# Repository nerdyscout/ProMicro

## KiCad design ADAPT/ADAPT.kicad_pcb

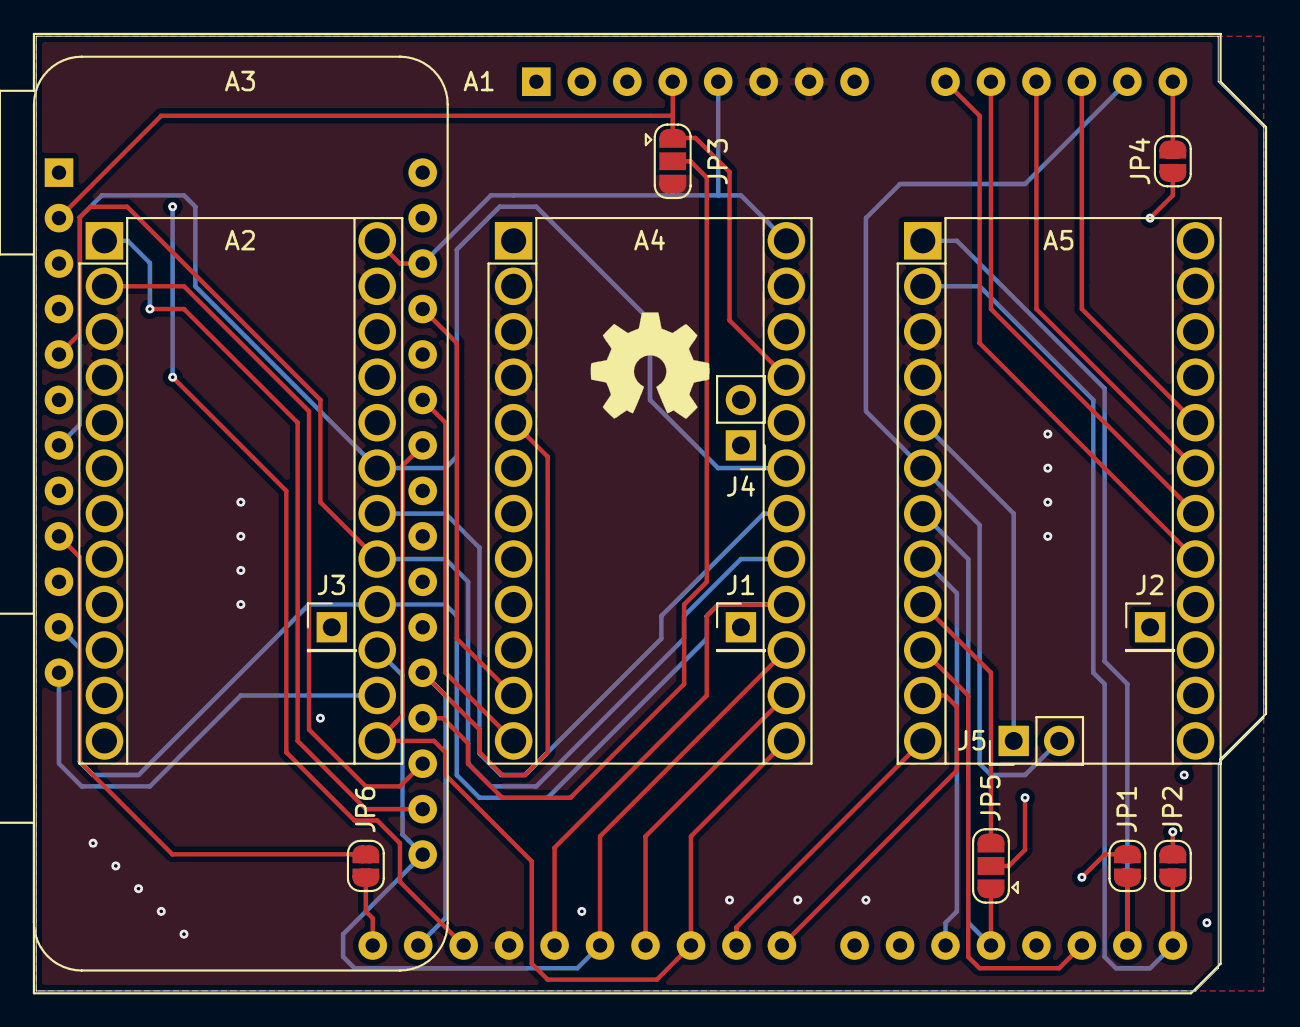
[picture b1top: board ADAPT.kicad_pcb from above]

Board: 4 copper layers, 68.6 x 53.3 mm, 17 parts (0 on the bottom side), 29 nets.

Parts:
A1: Arduino_UNO_R3
A2, A4, A5: Sparkfun_Pro_Micro; ProMicro
A3: Adafruit_Feather_Generic; Adafruit_Feather
J1, J2, J3: VBAT; PinHeader_1x01_P2.54mm_Vertical
J4, J5: Conn_01x02; PinHeader_1x02_P2.54mm_Vertical
JP1, JP2, JP4, JP6: SolderJumper_2_Open; SolderJumper-2_P1.3mm_Open_RoundedPad1.0x1.5mm
JP3, JP5: SolderJumper_3_Open; SolderJumper-3_P1.3mm_Open_RoundedPad1.0x1.5mm
LOGO1: Logo_Open_Hardware_Small; OSHW-Symbol_6.7x6mm_SilkScreen

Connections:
+3V3: A1.4, A2.21, A3.2, A4.21, A5.21, JP3.1
+5V: A1.5, A2.24, A3.26, A4.24, A5.24
A0: A1.9, A2.17, A3.5, A4.17, A5.17, JP5.2
A1: A1.10, A2.18, A3.6, A4.18, A5.18
A2: A1.11, A2.19, A3.7, A4.19, A5.19
A3: A1.12, A2.20, A3.8, A4.20, A5.20
AREF: A1.30, A3.3
BTN: A2.9, A4.9, A5.9, JP5.3
CIPO: A1.27, A2.15, A3.13, A4.15, A5.15
COPI: A1.26, A2.14, A3.12, A4.14, A5.14
CS0: A1.25, A2.13, A3.22, A4.13, A5.13
CS1: A1.24, A2.12, A3.23, A4.12, A5.12
D8: A1.23, A2.11, A3.25, A4.11, A5.11
GND: A1.6, A1.7, A1.29, A2.3, A2.4, A2.23, A3.4, A4.3, A4.4, A4.23, A5.3, A5.4, A5.23, JP3.3
INT: A1.17, A2.10, A3.21, A4.10, A5.10
unnamed: A3.9, JP6.1
unnamed: A3.10, JP4.1
unnamed: A3.19, JP1.2
unnamed: A3.20, JP2.2
unnamed: J1.1, J2.1, J3.1
PWM: A1.20, A2.8, A3.24, A4.8, A5.8
RXD: A1.16, A2.1, A3.14, A4.1, A5.1, JP1.1
SCK: A1.28, A2.16, A3.11, A4.16, A5.16
SCL: A1.13, A1.32, A2.6, A3.18, A4.6, A5.6, J4.2, J5.2, JP6.2
SDA: A1.14, A1.31, A2.5, A3.17, A4.5, A5.5, J4.1, J5.1, JP4.2
SPARE: A3.16, JP3.2
STAT: A1.19, A2.7, A4.7, A5.7, JP5.1
TXD: A1.15, A2.2, A3.15, A4.2, A5.2, JP2.1
~RST: A1.3, A2.22, A3.1, A4.22, A5.22

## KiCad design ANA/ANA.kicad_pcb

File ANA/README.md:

# ProMicro_ANA 
This module can be mounted, back on back, to any [Arduino Pro Mini](https://www.sparkfun.com/products/11113), [Arduino Nano](https://store.arduino.cc/arduino-nano) or [Sparkfun Pro Micro](https://www.sparkfun.com/products/12587) running with 3.3V. 

## Documentation 
All files can be found on [Github](https://github.com/nerdyscout/ProMicro/tree/master/ANA).

### Schematic

### BoM
  * [interactiveHTMLBoM](https://nerdyscout.github.io/ProMicro/ANA/docs/bom/ANA-ibom.html)
  * [octopart](docs/bom/ANA-bom_octopart.csv)

## Hardware 
### Layout

### Gerbers
can be found within the Github [repository](gerbers).

## Code  (unless otherwise stated)
  * [tbd](examples/tbd/tbd.ino)

## external
### Links
  * [hackaday.io](https://hackaday.io/project/171898-promicro)

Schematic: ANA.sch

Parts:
A1: Sparkfun_Pro_Micro
C1, C3: 10µ; C_0603_1608Metric
C2, C4: 4.7µ; C_0603_1608Metric
C5, C6: 100n; C_0603_1608Metric
D1, D2: LED; LED_0603_1608Metric
J1: Conn_01x04; TerminalBlock_Phoenix_MPT-0,5-4-2.54_1x04_P2.54mm_Horizontal
JP1, JP2, JP3, JP4: SolderJumper_2_Open; SolderJumper-2_P1.3mm_Open_RoundedPad1.0x1.5mm
L1, L2: 2.2µ; L_Bourns-SRN4018
LOGO1: Logo_Open_Hardware_Small; OSHW-Symbol_6.7x6mm_SilkScreen
R1, R3: 200k; R_0603_1608Metric
R2, R4: 47k; R_0603_1608Metric
R5, R6, R9, R10: 220; R_0603_1608Metric
R7: 4k7; R_0603_1608Metric; MPN RC0402FR-074K7L
R8: 4k7; R_0603_1608Metric; MPN RC0402FR-074K7L; lcsc# C105871
U1, U3: TLV62569DDC; SOT-23-6
U2, U4: MCP4725xxx-xCH; SOT-23-6
U5, U7: INA260; TSSOP-16_4.4x5mm_P0.65mm
U6: LTV-827S; SMDIP-8_W9.53mm

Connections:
A0: A1.17 (TDI/A0), C1.1, J1.3, JP3.1, L1.1, R1.2, R6.2, U5.1 (IN+), U5.2 (IN+), U5.3 (IN+), U5.12 (VBUS)
A1: A1.18 (TDO/A1), C3.1, J1.4, JP4.1, L2.1, R3.2, R10.2, U7.1 (IN+), U7.2 (IN+), U7.3 (IN+), U7.12 (VBUS)
GND: A1.3 (GND), A1.4 (GND), A1.23 (GND), C1.2, C2.2, C3.2, C4.2, C5.2, C6.2, D1.1 (K), D2.1 (K), JP1.2, R2.1, R4.1, U1.2 (GND), U2.2 (VSS), U2.6 (A0), U3.2 (GND), U4.2 (VSS), U5.4 (A1), U5.5 (A0), U5.6 (GND), U5.11 (GND), U6.2, U6.4, U7.5 (A0), U7.6 (GND), U7.11 (GND)
unnamed: C2.1, C4.1, J1.2, JP2.1, U1.1 (EN), U1.4 (VIN), U3.1 (EN), U3.4 (VIN)
unnamed: D1.2 (A), R5.1
unnamed: D2.2 (A), R9.1
unnamed: J1.1, JP1.1, U6.5, U6.7
unnamed: JP3.2, U5.14 (IN-), U5.15 (IN-), U5.16 (IN-), U6.6
unnamed: JP4.2, U6.8, U7.14 (IN-), U7.15 (IN-), U7.16 (IN-)
unnamed: L1.2, U1.3 (SW)
unnamed: L2.2, U3.3 (SW)
unnamed: R1.1, R2.2, U1.6 (FB), U2.1 (VOUT)
unnamed: R3.1, R4.2, U3.6 (FB), U4.1 (VOUT)
unnamed: R5.2, U5.7 (ALERT)
unnamed: R6.1, U6.1
unnamed: R9.2, U7.7 (ALERT)
unnamed: R10.1, U6.3
SCL: A1.6 (SCL/D3), R7.1, U2.5 (SCL), U4.5 (SCL), U5.9 (SCL), U7.9 (SCL)
SDA: A1.5 (SDA/D2), R8.1, U2.4 (SDA), U4.4 (SDA), U5.8 (SDA), U7.8 (SDA)
VCC: A1.21 (VCC), C5.1, C6.1, JP2.2, R7.2, R8.2, U2.3 (VDD), U4.3 (VDD), U4.6 (A0), U5.10 (VS), U7.4 (A1), U7.10 (VS)

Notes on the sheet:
opto isolated switch with current sensing
analog out
SCK
CIPO
COPI
CS0
CS1
STAT
PWM
BTN
INT
RXD
TXD
~RST
GND
Vin

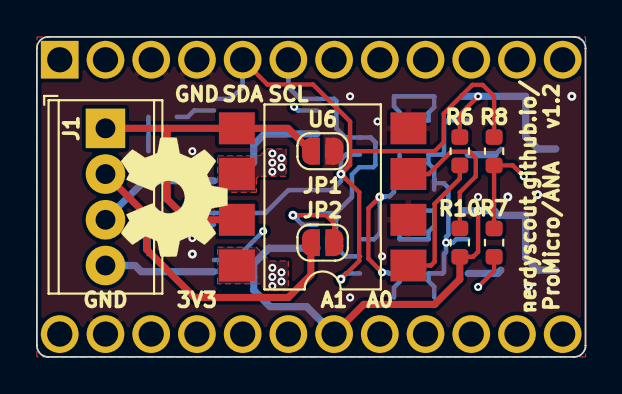
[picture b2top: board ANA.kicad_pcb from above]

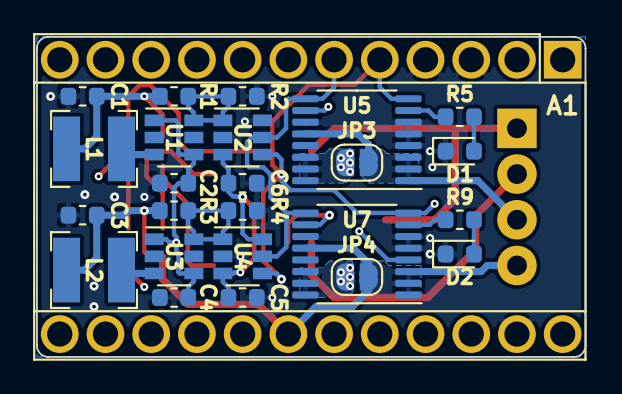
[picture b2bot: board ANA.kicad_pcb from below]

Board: 4 copper layers, 30.5 x 17.8 mm, 34 parts (25 on the bottom side), 20 nets.

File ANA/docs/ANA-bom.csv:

References;Description;Part;Value;Qty;mpn;lcsc#
A1;;Sparkfun_Pro_Micro;Sparkfun_Pro_Micro;1;;
C5 C6;Unpolarized capacitor;C;100n;2;;
C2 C4;Unpolarized capacitor;C;4.7µ;2;;
C1 C3;Unpolarized capacitor;C;10µ;2;;
D1 D2;Light emitting diode;LED;LED;2;;
J1;Generic connector, single row, 01x04, script generated (kicad-library-utils/schlib/autogen/connector/);Conn_01x04;Conn_01x04;1;;
L1 L2;Inductor;L;2.2µ;2;;
R5 R6 R9 R10;Resistor;R;220;4;;
R7 R8;Resistor;R;4k7;2;RC0402FR-074K7L;C105871
R2 R4;Resistor;R;47k;2;;
R1 R3;Resistor;R;200k;2;;
U5 U7;Current/power/voltage monitor with Integrated 2mΩ Shunt Resistor, 2.7V - 5.5V, I2C, TSSOP-16;INA260;INA260;2;;
U6;DC Optocoupler, Vce 35V, CTR 50%, SMDIP-8;LTV-827S;LTV-827S;1;;
U2 U4;12-bit Digital-to-Analog Converter, integrated EEPROM, I2C interface, SOT-23-6;MCP4725xxx-xCH;MCP4725xxx-xCH;2;;
U1 U3;High Efficiency Synchronous Buck Converter, Adjustable Output 0.6V-5.5V, 2A, SOT-23-6;TLV62569DDC;TLV62569DDC;2;;

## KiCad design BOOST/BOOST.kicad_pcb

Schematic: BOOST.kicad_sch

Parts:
A1: Sparkfun_Pro_Micro; ProMicro
C1, C4: 10µ; C_0603_1608Metric; MPN CL10A106KP8NNNC
C2, C5: 100n; C_0603_1608Metric; MPN CL10B104KO8NNNC
C3, C7: 4.7µ; C_0603_1608Metric; MPN CL10A475KO8NNNC
C6: 1µ; C_0603_1608Metric; MPN C0603X105K9RACAUTO
D1: D; D_0603_1608Metric
F1: 500mA; Fuse_0603_1608Metric; MPN 04000025WR
J1: JST; JST_PH_S2B-PH-SM4-TB_1x02-1MP_P2.00mm_Horizontal
JP1: SolderJumper_3_Open; SolderJumper-3_P1.3mm_Open_RoundedPad1.0x1.5mm
L1: 6.8µ/2A; L_Bourns_SRN6045TA; MPN 744787068
LOGO1: Logo_Open_Hardware_Small; OSHW-Symbol_6.7x6mm_SilkScreen
R1, R2, R6: 390k; R_0603_1608Metric; MPN 0603WAF3903T5E
R3: 2k; R_0603_1608Metric; MPN 0603WAF2001T5E
R4, R8: 200k; R_0603_1608Metric; MPN 0603WAF2003T5E
R5: 2.4M; R_0603_1608Metric; MPN WR06W2404FTL
R7: 1.1M; R_0603_1608Metric; MPN RM06FTN1104
TP1: VBAT; TestPoint_THTPad_D2.0mm_Drill1.0mm
U1: MCP73831-2-OT; SOT-23-5; MPN MCP73831T-2ACI/OT
U2: TPS61090; Texas_S-PVQFN-N16_EP2.7x2.7mm_ThermalVias; MPN TPS61090RSAR

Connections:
+3V3: A1.21, C6.1, C7.1, R7.1, U2.1 (VOUT), U2.15 (VOUT), U2.16 (VOUT)
/EN: R4.1, U2.11 (EN)
/VBAT: C3.2, C4.2, C5.1, J1.1, L1.1, R1.1, R4.2, R5.1, TP1.1, U1.3 (V_{BAT}), U2.8 (VBAT)
GND: A1.3, A1.4, A1.23, C1.2, C2.1, C3.1, C4.1, C5.2, C6.2, C7.2, J1.2, R2.2, R3.1, R6.2, R8.2, U1.2 (V_{SS}), U2.5 (PGND), U2.6 (PGND), U2.7 (PGND), U2.10 (SYNC), U2.13 (GND), U2.17 (PAD)
LBO: JP1.3 (B), U2.12 (LBO)
unnamed: C1.1, C2.2, D1.1 (K), U1.4 (V_{DD})
unnamed: D1.2 (A), F1.2
unnamed: JP1.1 (A), R1.2, R2.1
unnamed: L1.2, U2.3 (SW), U2.4 (SW)
unnamed: R3.2, U1.5 (PROG)
unnamed: R5.2, R6.1, U2.9 (LBI)
unnamed: R7.2, R8.1, U2.14 (FB)
STAT: A1.7, JP1.2 (C)
VBUS: A1.24, F1.1

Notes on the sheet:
R7 1.85M 1.1M (default)
Vout 5 3,3
LBI/LBO Threshold Voltage
Output Voltage
R7 = R8 * ((Vout/Vfb) -1)
R6 390k (default) 390k 390k 200k
close 1-2 read analog voltage close 2-3 read LBO status open 1 2 3 if no battery status required
R3 Icharge 2k 500mA (default) 1k 1000mA
Do only populate if you want to read analog battery voltage
R5 = R6 * ((VBat/500mV) -1)
R5 2.4M 2.5M 2.6M 1.3M
VBat 3.6 3.7 3.8 3.75
R8 200k 200k

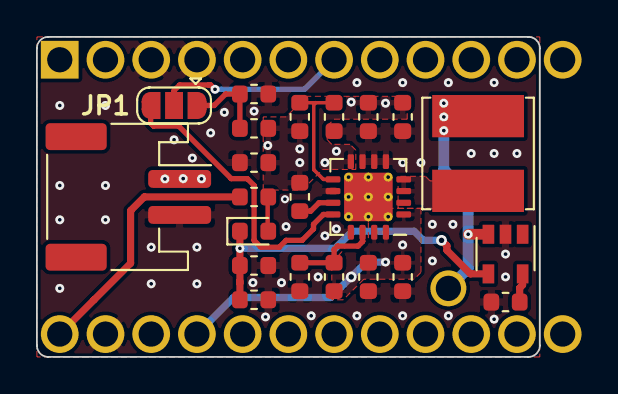
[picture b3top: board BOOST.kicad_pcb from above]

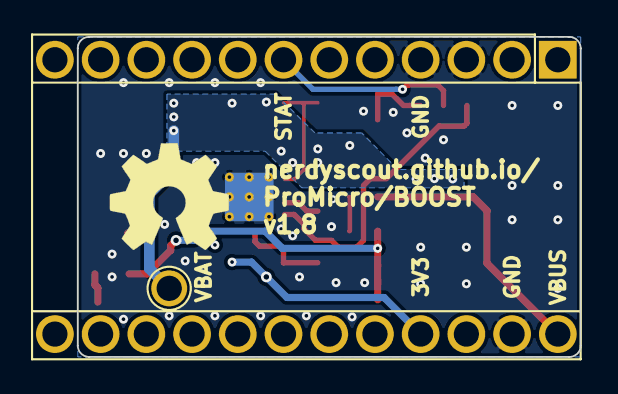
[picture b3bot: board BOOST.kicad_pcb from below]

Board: 4 copper layers, 27.9 x 17.8 mm, 25 parts (3 on the bottom side), 14 nets.

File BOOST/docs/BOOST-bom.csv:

References;Description;Part;Value;Qty;mpn;variant
C2 C5;Unpolarized capacitor;C;100n;2;CL10B104KO8NNNC;3V3, 5V
C6;Unpolarized capacitor;C;1µ;1;C0603X105K9RACAUTO;
C3 C7;Unpolarized capacitor;C;4.7µ;2;CL10A475KO8NNNC;
C1 C4;Unpolarized capacitor;C;10µ;2;CL10A106KP8NNNC;3V3, 5V
D1;Diode;D;D;1;;3V3, 5V
F1;Fuse;Fuse;500mA;1;04000025WR;
J1;Generic connector, single row, 01x02, script generated (kicad-library-utils/schlib/autogen/connector/);Conn_01x02;JST;1;;3V3, 5V
L1;Inductor;L;6.8µ/2A;1;744787068;
R3;Resistor;R;2k;1;0603WAF2001T5E;
R4 R8;Resistor;R;200k;2;0603WAF2003T5E;
R1 R2 R6;Resistor;R;390k;3;0603WAF3903T5E;
R7;Resistor;R;1.1M;1;RM06FTN1104;
R5;Resistor;R;2.4M;1;WR06W2404FTL;
U1;Single cell, Li-Ion/Li-Po charge management controller, 4.20V, Tri-State Status Output, in SOT23-5 package;MCP73831-2-OT;MCP73831-2-OT;1;MCP73831T-2ACI/OT;3V3, 5V
U2;2A Step-Up DC-DC Converter for Batteries, Isw up to 2500mA, Adjustable output voltage, QFN-16;TPS61090;TPS61090;1;TPS61090RSAR;3V3, 5V

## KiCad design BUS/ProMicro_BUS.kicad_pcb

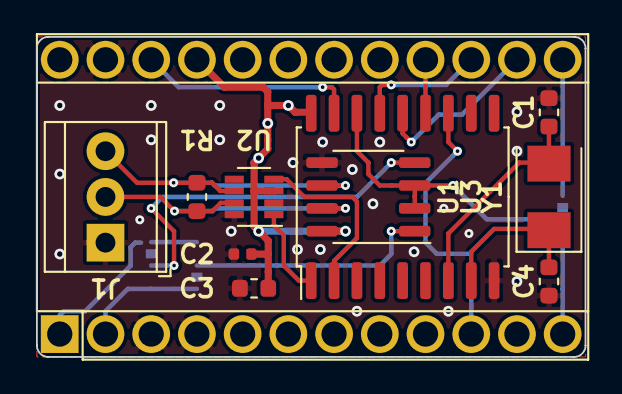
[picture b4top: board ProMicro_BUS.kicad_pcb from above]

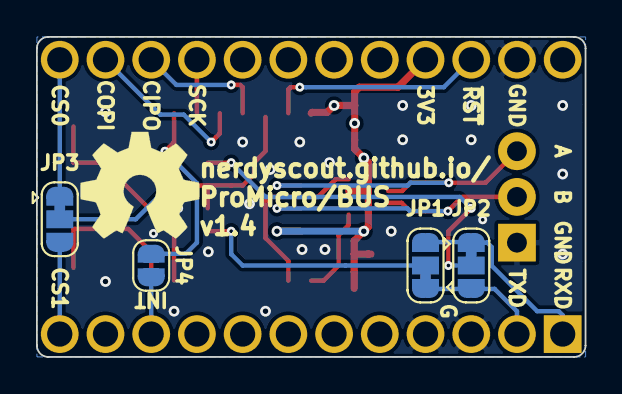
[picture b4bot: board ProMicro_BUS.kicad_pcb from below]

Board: 2 copper layers, 30.5 x 17.8 mm, 16 parts (5 on the bottom side), 21 nets.

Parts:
A1: Sparkfun_Pro_Micro
C1, C4: C; C_0603_1608Metric
C2: 100n; C_0402_1005Metric
C3: 10µ; C_0603_1608Metric
J1: Conn_01x03; TerminalBlock_TE_282834-3_1x03_P2.54mm_Horizontal
JP1, JP2, JP3: SolderJumper_3_Bridged12; SolderJumper-3_P1.3mm_Bridged12_RoundedPad1.0x1.5mm
JP4: SolderJumper_2_Open; SolderJumper-2_P1.3mm_Open_RoundedPad1.0x1.5mm
LOGO1: Logo_Open_Hardware_Small; OSHW-Symbol_6.7x6mm_SilkScreen
R1: 120; R_0603_1608Metric
U1: MAX3483; SO-8_3.9x4.9mm_P1.27mm
U2: MAX3051; SOT-23-8
U3: MCP2515-xSO; SOIC-18W_7.5x11.6mm_P1.27mm
Y1: Crystal; Crystal_SMD_5032-2Pin_5.0x3.2mm

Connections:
+3V3: A1.21, C2.1, C3.1, U1.8, U2.3, U3.18
/A: J1.3, R1.2, U1.6, U2.6
/B: J1.2, R1.1, U1.7, U2.7
CIPO: A1.15, U3.15
COPI: A1.14, U3.14
CS: JP3.2, U1.2, U1.3, U3.16
CS0: A1.13, JP3.1
CS1: A1.12, JP3.3
GND: A1.3, A1.4, A1.23, C1.1, C2.2, C3.2, C4.2, J1.1, U1.5, U2.2, U2.8, U3.9
INT: A1.10, JP4.2
unnamed: C1.2, U3.7, Y1.2
unnamed: C4.1, U3.8, Y1.1
unnamed: JP1.2, U1.1
unnamed: JP2.2, U1.4
unnamed: JP4.1, U3.12
unnamed: U2.1, U3.1
unnamed: U2.4, U3.2
RXD: A1.1, JP1.3, JP2.1
SCK: A1.16, U3.13
TXD: A1.2, JP1.1, JP2.3
~RST: A1.22, U3.17

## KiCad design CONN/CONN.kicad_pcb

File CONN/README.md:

# ProMicro_CONN 
This module can be mounted to an [Arduino Pro Mini](https://www.sparkfun.com/products/11113), [Arduino Nano](https://store.arduino.cc/arduino-nano), [Sparkfun Pro Micro](https://www.sparkfun.com/products/12587), or any other pincompatible MCU running with 3.3V. You could connect a 0.91" OLED Display and a UEXT connector for more modules, alternatively a JTAG socket is available.

## Documentation 
All files can be found on [Github](https://github.com/nerdyscout/ProMicro/tree/master/CONN).

### Schematic

### BoM
  * [interactiveHTMLBoM](https://nerdyscout.github.io/ProMicro/CONN/docs/bom/CONN-ibom.html)
  * [octopart](pcb/docs/bom/CONN-bom_octopart.csv)

## Hardware 
### Layout

### Gerbers
can be found within the Github [repository](pcb/gerbers).

## Code  (unless otherwise stated)
  * [LCD](examples/LCD/LCD.ino)

## external
### Links
  * [hackaday.io](https://hackaday.io/project/171898-promicro)

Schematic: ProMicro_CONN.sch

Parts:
A1: Sparkfun_Pro_Micro
C2: 1µ; C_0603_1608Metric; MPN CL10A105KB8NNNC; LCSC# C15849
C3: 100n; C_0603_1608Metric; MPN CC0603KRX7R9BB104; LCSC# C14663
D1: LED; LED_0603_1608Metric; MPN 19-217/GHC-YR1S2/3T; LCSC# C72043
J1: AVR-JTAG-10; IDC-Header_2x05_P2.54mm_Vertical
J2: UEXT_Host; UEXT
J3: Display; PinHeader_1x04_P2.54mm_Vertical
LOGO1: Logo_Open_Hardware_Small; OSHW-Symbol_6.7x6mm_SilkScreen
R1, R2, R3, R4, R5, R6, R7, R9: 4k7; R_0603_1608Metric; MPN 0603WAF4701T5E; LCSC# C23162
R8: 1k; R_0603_1608Metric
SW1: reset; SW_SPST_B3U-1000P; MPN B3U-1000P
SW2: user; SW_SPST_B3U-1000P; MPN B3U-1000P

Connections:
+3V3: A1.21, C3.1, J1.4 (VREF), J1.7 (VCC), J2.1 (3V3), J3.2, R1.2, R2.2, R3.2, R4.2, R5.2, R6.2, R7.2
+5V: A1.24
BTN: A1.9, SW2.2; also elsewhere on the board
CIPO: A1.15, J2.7 (MISO)
COPI: A1.14, J2.8 (MOSI)
CS1: A1.12, J2.10 (~SSEL)
GND: A1.3, A1.4, A1.23, C2.2, C3.2, D1.1 (K), J1.2 (GND), J1.10 (GND), J2.2 (GND), J3.1, R9.1, SW1.1
unnamed: D1.2 (A), R8.1
unnamed 14: R9.2, SW2.1; also elsewhere on the board
RXD: A1.1, J2.4 (RXD)
SCK: A1.16, J2.9 (SCK)
SCL: A1.6, J2.5 (SCL), J3.3, R3.1
SDA: A1.5, J2.6 (SDA), J3.4, R4.1
TCK: A1.20, J1.1 (TCK), R6.1, R8.2
TDI: A1.17, J1.9 (TDI), R1.1
TDO: A1.18, J1.3 (TDO), R2.1
TMS: A1.19, J1.5 (TMS), R5.1
TXD: A1.2, J2.3 (TXD)
~RST: A1.22, C2.1, J1.6 (~SRST), R7.1, SW1.2

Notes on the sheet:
Attention: RXD & TXD are swapped here!
uses internal pull-up

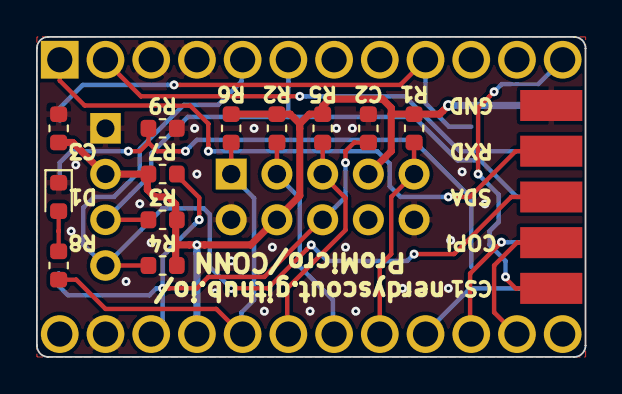
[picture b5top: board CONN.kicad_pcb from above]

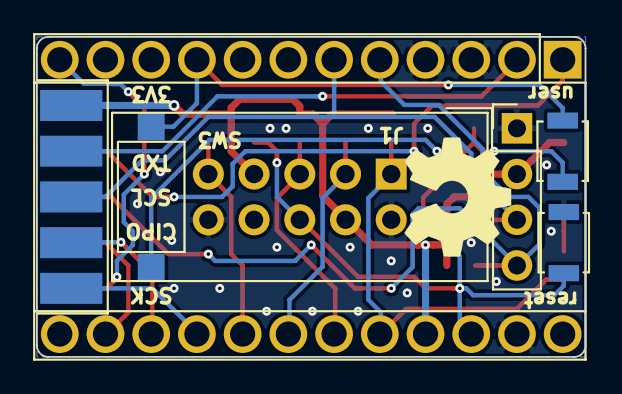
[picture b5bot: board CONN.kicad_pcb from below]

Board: 4 copper layers, 30.5 x 17.8 mm, 20 parts (8 on the bottom side), 18 nets.

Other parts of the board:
SW3: user; SW_SPST_CK_RS282G05A3

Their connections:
BTN: SW3.2; also elsewhere on the board
unnamed 14: SW3.1; also elsewhere on the board

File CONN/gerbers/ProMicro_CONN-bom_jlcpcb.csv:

Comment,Designator,Package,lcsc#,mpn
Sparkfun_Pro_Micro,A1,Sparkfun_Pro_Micro,,
100n,C3,C_0603_1608Metric,C14663,CC0603KRX7R9BB104
1µ,C2,C_0603_1608Metric,C15849,CL10A105KB8NNNC
LED,D1,LED_0603_1608Metric,C72043,19-217/GHC-YR1S2/3T
AVR-JTAG-10,J1,IDC-Header_2x05_P2.54mm_Vertical,,
Display,J3,PinHeader_1x04_P2.54mm_Vertical,,
UEXT_Host,J2,UEXT,,
Logo_Open_Hardware_Small,LOGO1,OSHW-Symbol_6.7x6mm_SilkScreen,,
1k,R8,R_0603_1608Metric,,
4k7,R1,R_0603_1608Metric,C23162,0603WAF4701T5E
4k7,R2,R_0603_1608Metric,C23162,0603WAF4701T5E
4k7,R3,R_0603_1608Metric,C23162,0603WAF4701T5E
4k7,R4,R_0603_1608Metric,C23162,0603WAF4701T5E
4k7,R5,R_0603_1608Metric,C23162,0603WAF4701T5E
4k7,R6,R_0603_1608Metric,C23162,0603WAF4701T5E
4k7,R7,R_0603_1608Metric,C23162,0603WAF4701T5E
4k7,R9,R_0603_1608Metric,C23162,0603WAF4701T5E
reset,SW1,SW_SPST_B3U-1000P,,B3U-1000P
user,SW2,SW_SPST_B3U-1000P,,B3U-1000P

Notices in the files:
ANA/README.md:
Documentation [![CC BY-SA](../img/ccbysa.png)](docs/LICENSE.TXT):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
CONN/README.md:
Documentation [![CC BY-SA](../img/ccbysa.png)](pcb/docs/LICENSE.TXT):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
